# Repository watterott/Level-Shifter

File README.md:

# Level-Shifter
Logic Level Shifters in different configurations.

* Open-Source and released under the [Creative Commons Attribution Share-Alike License](https://creativecommons.org/licenses/by-sa/4.0/).
* **[Documentation on learn.watterott.com](https://learn.watterott.com)**

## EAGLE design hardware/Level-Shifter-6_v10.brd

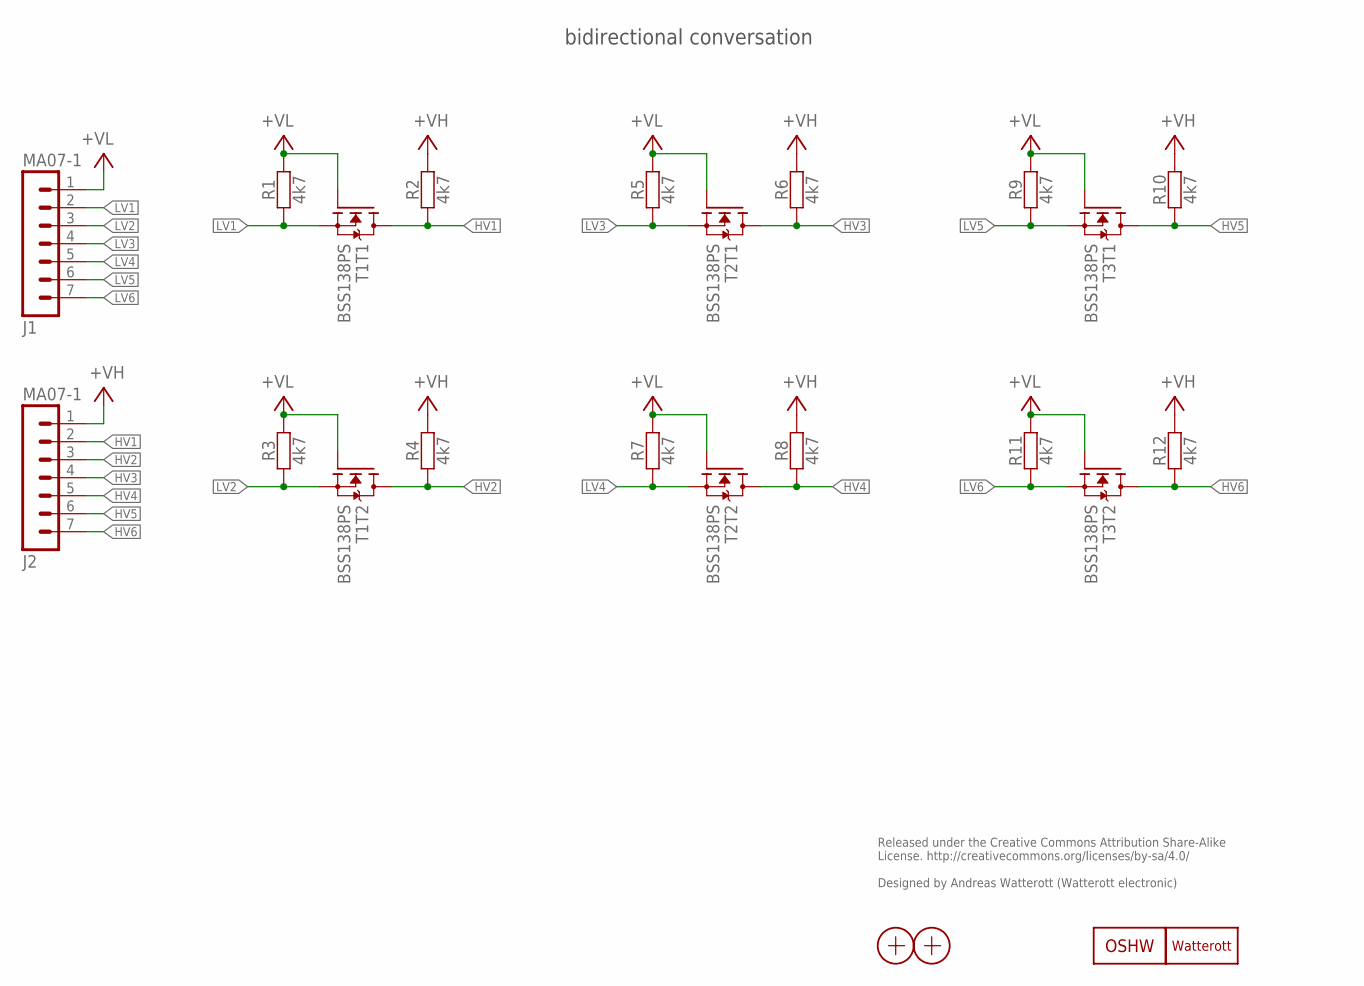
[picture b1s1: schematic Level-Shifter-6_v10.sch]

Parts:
J1, J2: MA07-1
LOGO1: OSHW_LOGOX0070; OSHW_6X70
LOGO2: LOGO-S_PLACE_S; SPARK_TPLACE_S
R1, R2, R3, R4, R5, R6, R7, R8, R9, R10, R11, R12: 4k7; C0402
T1, T2, T3: BSS138PS; SOT363
X1, X2: PASSER-07; PASSER_07MM

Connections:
+VH: J2.1, R2.2, R4.2, R6.2, R8.2, R10.2, R12.2
+VL: J1.1, R1.2, R3.2, R5.2, R7.2, R9.2, R11.2, T1.2 (G), T1.5 (G), T2.2 (G), T2.5 (G), T3.2 (G), T3.5 (G)
HV1: J2.2, R2.1, T1.6 (D)
HV2: J2.3, R4.1, T1.3 (D)
HV3: J2.4, R6.1, T2.6 (D)
HV4: J2.5, R8.1, T2.3 (D)
HV5: J2.6, R10.1, T3.6 (D)
HV6: J2.7, R12.1, T3.3 (D)
LV1: J1.2, R1.1, T1.1 (S)
LV2: J1.3, R3.1, T1.4 (S)
LV3: J1.4, R5.1, T2.1 (S)
LV4: J1.5, R7.1, T2.4 (S)
LV5: J1.6, R9.1, T3.1 (S)
LV6: J1.7, R11.1, T3.4 (S)

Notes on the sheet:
Released under the Creative Commons Attribution Share-Alike License. http://creativecommons.org/licenses/by-sa/4.0/ Designed by Andreas Watterott (Watterott electronic)
bidirectional conversation

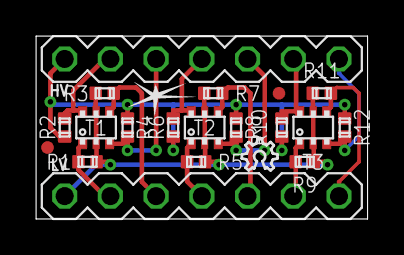
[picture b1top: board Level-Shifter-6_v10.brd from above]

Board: 2 copper layers, 18.4 x 10.2 mm, 21 parts (0 on the bottom side), 14 nets.

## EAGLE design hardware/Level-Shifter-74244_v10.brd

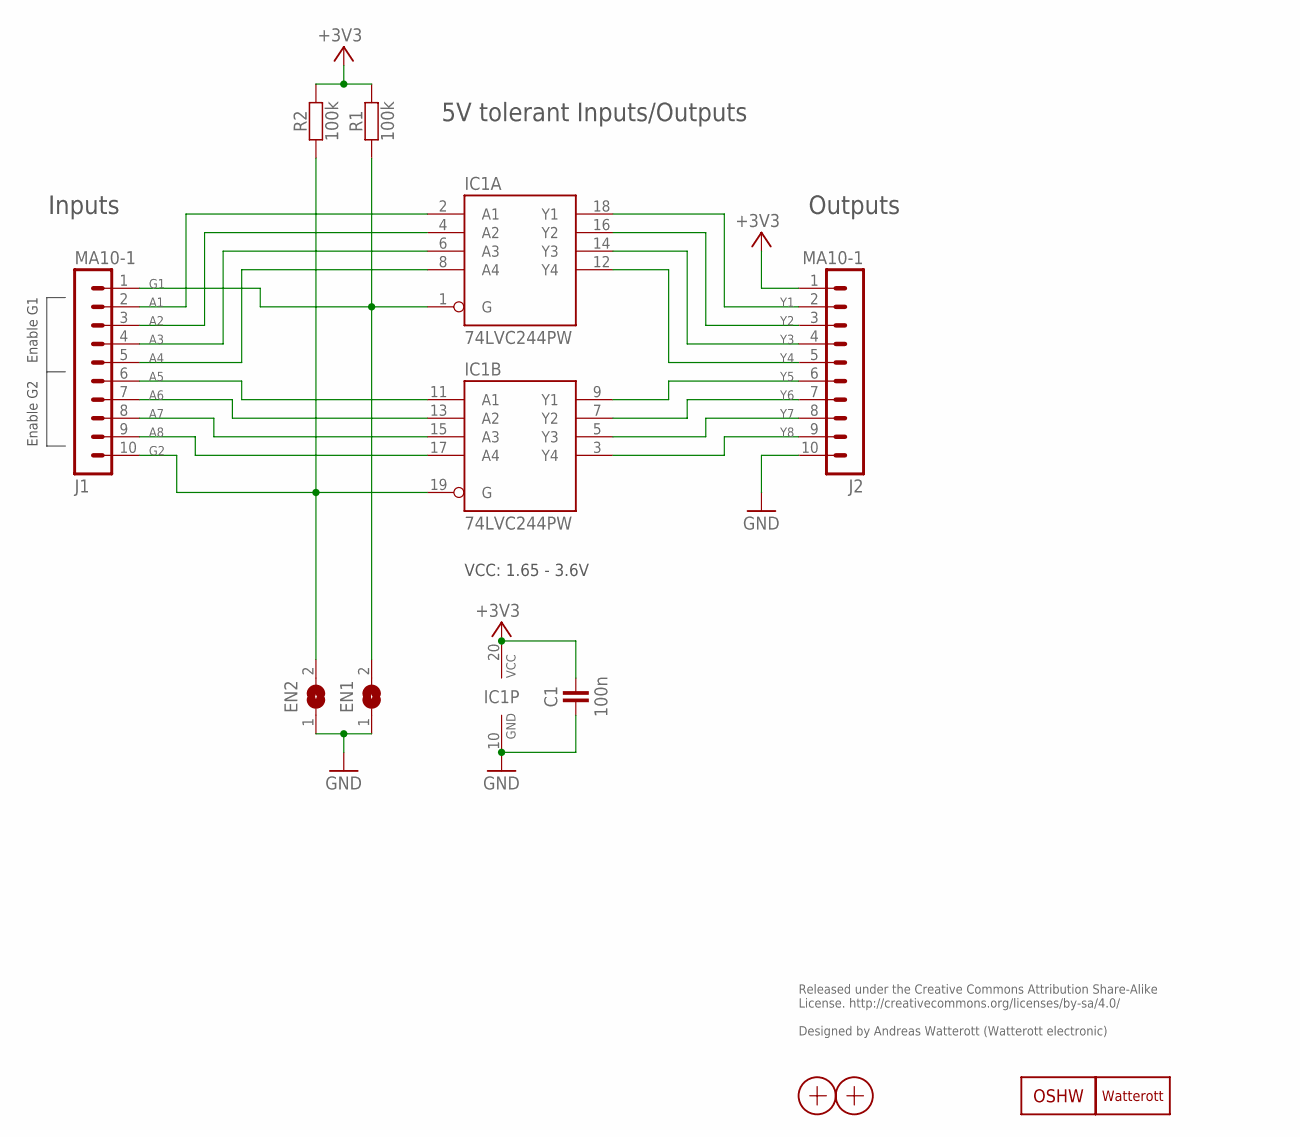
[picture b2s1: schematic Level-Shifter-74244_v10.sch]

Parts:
C1: 100n; C0402
EN1, EN2: JUMPER2-0603-NC; JUMPER2-0603_NC
IC1: 74LVC244PW; TSSOP20
J1, J2: MA10-1
LOGO1: OSHW_LOGOX0070; OSHW_6X70
LOGO2: LOGO-S_PLACE_S; SPARK_TPLACE_S
R1, R2: 100k; C0402
X1, X2: PASSER-07; PASSER_07MM

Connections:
+3V3: C1.2, IC1.20 (VCC), J2.1, R1.2, R2.2
A1: IC1.2 (A1), J1.2
A2: IC1.4 (A2), J1.3
A3: IC1.6 (A3), J1.4
A4: IC1.8 (A4), J1.5
A5: IC1.11 (A1), J1.6
A6: IC1.13 (A2), J1.7
A7: IC1.15 (A3), J1.8
A8: IC1.17 (A4), J1.9
G1: EN1.2, IC1.1 (G), J1.1, R1.1
G2: EN2.2, IC1.19 (G), J1.10, R2.1
GND: C1.1, EN1.1, EN2.1, IC1.10 (GND), J2.10
Y1: IC1.18 (Y1), J2.2
Y2: IC1.16 (Y2), J2.3
Y3: IC1.14 (Y3), J2.4
Y4: IC1.12 (Y4), J2.5
Y5: IC1.9 (Y1), J2.6
Y6: IC1.7 (Y2), J2.7
Y7: IC1.5 (Y3), J2.8
Y8: IC1.3 (Y4), J2.9

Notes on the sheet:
Released under the Creative Commons Attribution Share-Alike License. http://creativecommons.org/licenses/by-sa/4.0/ Designed by Andreas Watterott (Watterott electronic)
VCC: 1.65 - 3.6V
Enable G1
Enable G2
Inputs
Outputs
5V tolerant Inputs/Outputs

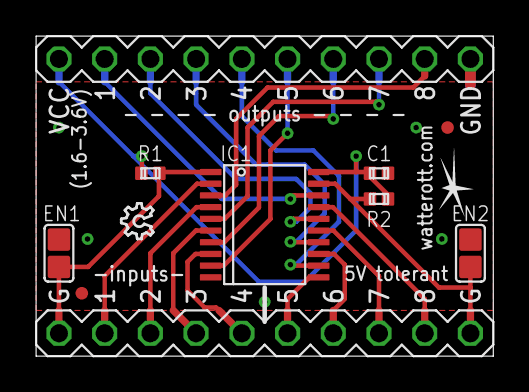
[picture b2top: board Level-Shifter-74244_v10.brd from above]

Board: 2 copper layers, 25.4 x 17.8 mm, 12 parts (0 on the bottom side), 20 nets.

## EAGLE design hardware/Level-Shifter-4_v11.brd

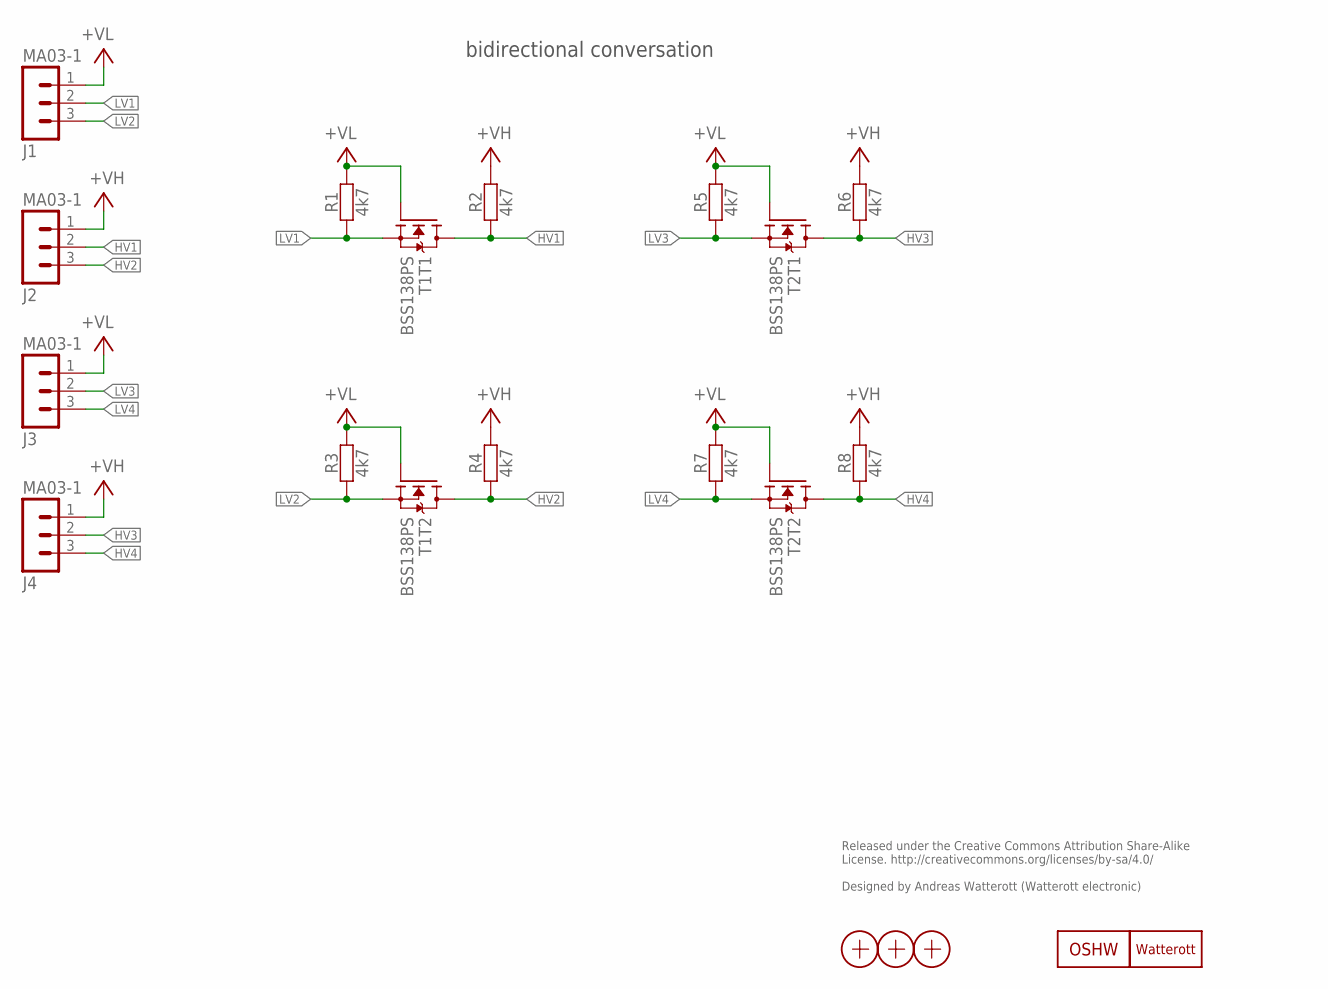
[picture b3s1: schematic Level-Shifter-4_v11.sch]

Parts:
J1, J2, J3, J4: MA03-1
LOGO1: OSHW_LOGOX0070; OSHW_6X70
LOGO2: LOGO-S_PLACE_S; SPARK_TPLACE_S
R1, R2, R3, R4, R5, R6, R7, R8: 4k7; C0402
T1, T2: BSS138PS; SOT363
X1, X2, X3: PASSER-07; PASSER_07MM

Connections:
+VH: J2.1, J4.1, R2.2, R4.2, R6.2, R8.2
+VL: J1.1, J3.1, R1.2, R3.2, R5.2, R7.2, T1.2 (G), T1.5 (G), T2.2 (G), T2.5 (G)
HV1: J2.2, R2.1, T1.6 (D)
HV2: J2.3, R4.1, T1.3 (D)
HV3: J4.2, R6.1, T2.6 (D)
HV4: J4.3, R8.1, T2.3 (D)
LV1: J1.2, R1.1, T1.1 (S)
LV2: J1.3, R3.1, T1.4 (S)
LV3: J3.2, R5.1, T2.1 (S)
LV4: J3.3, R7.1, T2.4 (S)

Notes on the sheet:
Released under the Creative Commons Attribution Share-Alike License. http://creativecommons.org/licenses/by-sa/4.0/ Designed by Andreas Watterott (Watterott electronic)
bidirectional conversation

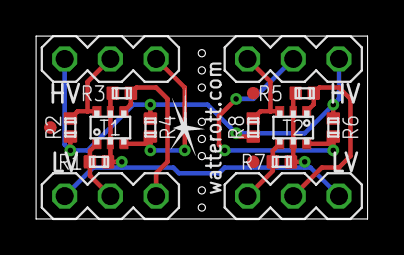
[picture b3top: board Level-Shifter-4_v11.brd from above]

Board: 2 copper layers, 18.4 x 10.2 mm, 19 parts (1 on the bottom side), 10 nets.

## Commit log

2017-08-10 updated readme and photos
2017-08-10 updated schematics
